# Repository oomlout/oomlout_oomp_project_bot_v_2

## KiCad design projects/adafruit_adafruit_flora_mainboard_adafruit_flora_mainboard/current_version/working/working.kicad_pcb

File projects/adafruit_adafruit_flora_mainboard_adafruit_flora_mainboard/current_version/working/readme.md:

# adafruit_flora_mainboard
 
## summary 
* id: adafruit_adafruit_flora_mainboard_adafruit_flora_mainboard
* user: adafruit
* name: adafruit_flora_mainboard
* board: adafruit_flora_mainboard
* repo: https://github.com/adafruit/Adafruit-Flora-Mainboard

* src_file_repo_sch: 
* src_file_repo_sch_link: https://github.com/adafruit/Adafruit-Flora-Mainboard/tree/master/
* full details link: https://github.com/oomlout/oomlout_oomp_project_bot_v_2/tree/main/projects/adafruit_adafruit_flora_mainboard_adafruit_flora_mainboard/current_version/working  

## schematic  
  
[schematic (pdf)](working_schematic.pdf) 

## pcb  

[board (pdf)](working.pdf)  

## working_bom
| Id | Designator | Footprint | Quantity | Designation | Supplier and ref |  | None | 
| --- | --- | --- | --- | --- | --- | --- | --- | 
| 1 | TXLED0,RXLED0 | CHIPLED_0805_NOOUTLINE | 2 | YELLOW |  |  | [''] | 
| 2 | R1,R2 | 0805-NO | 2 | 22 |  |  | [''] | 
| 3 | ON/OFF0 | EG1390 | 1 | EG1390 |  |  | [''] | 
| 4 | R4,R3 | _0805MP | 2 | 1K |  |  | [''] | 
| 5 | IC2 | SOT23-5L | 1 | MIC5225-3.3V |  |  | [''] | 
| 6 | TX0,RX0,UNK3.3VTAP0,UNK3V3TAP2,VCC2,GNDTAP0,GNDTAP2,SDA0,GND3TAP0,D6,IO9,SCL0,IO12,IO10 | SEWINGTAP_2.0 | 14 | SEWTAP-2.0IN |  |  | [''] | 
| 7 | C6,C4,C8,C7,C5 | 0805-NO | 5 | 10uF |  |  | [''] | 
| 8 | U$2,U$3,U$6 | FIDUCIAL_1MM | 3 | FIDUCIAL" |  |  | [''] | 
| 9 | U$1 | ADAFRUIT_5MM | 1 |  |  |  | [''] | 
| 10 | Y1 | RESONATOR-SMD | 1 | 8MHz |  |  | [''] | 
| 11 | R7 | _0805MP | 1 | 10K |  |  | [''] | 
| 12 | JP1 | 2X03 | 1 | ICSP |  |  | [''] | 
| 13 | R8 | 0805-NO | 1 | 150K |  |  | [''] | 
| 14 | D2,D1 | SOD-123 | 2 | SCHOTTKY |  |  | [''] | 
| 15 | CN1 | 4UCONN_20329 | 1 | MiniB USB |  |  | [''] | 
| 16 | LED1 | WS2812 | 1 | WS2812 |  |  | [''] | 
| 17 | BOOT0 | KMR2 | 1 | SPST_TACT-KMR2 |  |  | [''] | 
| 18 | C9 | _0805MP | 1 | 10uF |  |  | [''] | 
| 19 | R9 | 0805-NO | 1 | 10K |  |  | [''] | 
| 20 | R5,R6 | 0805-NO | 2 | 1K |  |  | [''] | 
| 21 | L0 | CHIPLED_0805_NOOUTLINE | 1 | RED |  |  | [''] | 
| 22 | BATT0 | JST-PH-2-SMT-RA | 1 | 3-9VDC |  |  | [''] | 
| 23 | PWR0 | CHIPLED_0805_NOOUTLINE | 1 | GREEN |  |  | [''] | 
| 24 | R10 | 0805-NO | 1 | 2.2K |  |  | [''] | 
| 25 | L1 | R1206 | 1 | 500mA |  |  | [''] | 
| 26 | T1 | SOT-23 | 1 | DMG3415 |  |  | [''] | 
| 27 | IC1 | TQFP44 | 1 | ATMEGA32U4-AU |  |  | [''] | 
| 28 | U$8 | SYMBOL_CE_5MM | 1 |  |  |  | [''] | 
| 29 | U$5 | PCBFEAT-REV-040 | 1 |  |  |  | [''] | 
| 30 | U$7 | SYMBOL_FCC_5MM | 1 |  |  |  | [''] | 
| 31 | U$4 | FLORAMED | 1 |  |  |  | [''] | 

## bom_schematic
| Ref | Qnty | Value | Cmp name | Footprint | Description | Vendor | DNP | 
| --- | --- | --- | --- | --- | --- | --- | --- | 
| BATT0 | 1 | 3-9VDC | JST_2PIN-SMT-RA | working:JST-PH-2-SMT-RA |  |  |  | 
| BOOT0 | 1 | SPST_TACT-KMR2 | SPST_TACT-KMR2 | working:KMR2 |  |  |  | 
| C4, C5, C6, C7, C8 | 5 | 10uF | CAP_CERAMIC0805-NOOUTLINE | working:0805-NO |  |  |  | 
| C9 | 1 | 10uF | RESISTOR_0805MP | working:_0805MP |  |  |  | 
| CN1 | 1 | MiniB USB | USBMICRO_20329 | working:4UCONN_20329 |  |  |  | 
| D1, D2 | 2 | SCHOTTKY | DIODESOD-123 | working:SOD-123 |  |  |  | 
| D6 | 1 | SEWTAP-2.0IN | SEWTAP-2.0IN | working:SEWINGTAP_2.0 |  |  |  | 
| GND3TAP0 | 1 | SEWTAP-2.0IN | SEWTAP-2.0IN | working:SEWINGTAP_2.0 |  |  |  | 
| GNDTAP0, GNDTAP2 | 2 | SEWTAP-2.0IN | SEWTAP-2.0IN | working:SEWINGTAP_2.0 |  |  |  | 
| IC1 | 1 | ATMEGA32U4-AU | ATMEGA32U4-AU | working:TQFP44 |  |  |  | 
| IC2 | 1 | LP298XS | LP298XS | working:SOT23-5L |  |  |  | 
| IO9, IO10, IO12 | 3 | SEWTAP-2.0IN | SEWTAP-2.0IN | working:SEWINGTAP_2.0 |  |  |  | 
| JP1 | 1 | ICSP | PINHD-2X3 | working:2X03 |  |  |  | 
| L0 | 1 | RED | LED0805_NOOUTLINE | working:CHIPLED_0805_NOOUTLINE |  |  |  | 
| L1 | 1 | 500mA | PTCFUSE-1206 | working:R1206 |  |  |  | 
| LED1 | 1 | WS2812 | WS2812 | working:WS2812 |  |  |  | 
| ON/OFF0 | 1 | EG1390 | DPDT-EG1390 | working:EG1390 |  |  |  | 
| PWR0 | 1 | GREEN | LED0805_NOOUTLINE | working:CHIPLED_0805_NOOUTLINE |  |  |  | 
| R1, R2 | 2 | 22 | RESISTOR0805_NOOUTLINE | working:0805-NO |  |  |  | 
| R3, R4 | 2 | 1K | RESISTOR_0805MP | working:_0805MP |  |  |  | 
| R5, R6 | 2 | 1K | RESISTOR0805_NOOUTLINE | working:0805-NO |  |  |  | 
| R7 | 1 | 10K | RESISTOR_0805MP | working:_0805MP |  |  |  | 
| R8 | 1 | 150K | RESISTOR0805_NOOUTLINE | working:0805-NO |  |  |  | 
| R9 | 1 | 10K | RESISTOR0805_NOOUTLINE | working:0805-NO |  |  |  | 
| R10 | 1 | 2.2K | RESISTOR0805_NOOUTLINE | working:0805-NO |  |  |  | 
| RX0 | 1 | SEWTAP-2.0IN | SEWTAP-2.0IN | working:SEWINGTAP_2.0 |  |  |  | 
| RXLED0 | 1 | YELLOW | LED0805_NOOUTLINE | working:CHIPLED_0805_NOOUTLINE |  |  |  | 
| SCL0 | 1 | SEWTAP-2.0IN | SEWTAP-2.0IN | working:SEWINGTAP_2.0 |  |  |  | 
| SDA0 | 1 | SEWTAP-2.0IN | SEWTAP-2.0IN | working:SEWINGTAP_2.0 |  |  |  | 
| T1 | 1 | DMG3415 | PMOSSOT23 | working:SOT-23 |  |  |  | 
| TX0 | 1 | SEWTAP-2.0IN | SEWTAP-2.0IN | working:SEWINGTAP_2.0 |  |  |  | 
| TXLED0 | 1 | YELLOW | LED0805_NOOUTLINE | working:CHIPLED_0805_NOOUTLINE |  |  |  | 
| U$2, U$3, U$6 | 3 | FIDUCIAL"" | FIDUCIAL{dblquote}{dblquote} | working:FIDUCIAL_1MM |  |  |  | 
| UNK3.3VTAP0 | 1 | SEWTAP-2.0IN | SEWTAP-2.0IN | working:SEWINGTAP_2.0 |  |  |  | 
| UNK3V3TAP2 | 1 | SEWTAP-2.0IN | SEWTAP-2.0IN | working:SEWINGTAP_2.0 |  |  |  | 
| VCC2 | 1 | SEWTAP-2.0IN | SEWTAP-2.0IN | working:SEWINGTAP_2.0 |  |  |  | 
| Y1 | 1 | RESONATORSMD | RESONATORSMD | working:RESONATOR-SMD |  |  |  |

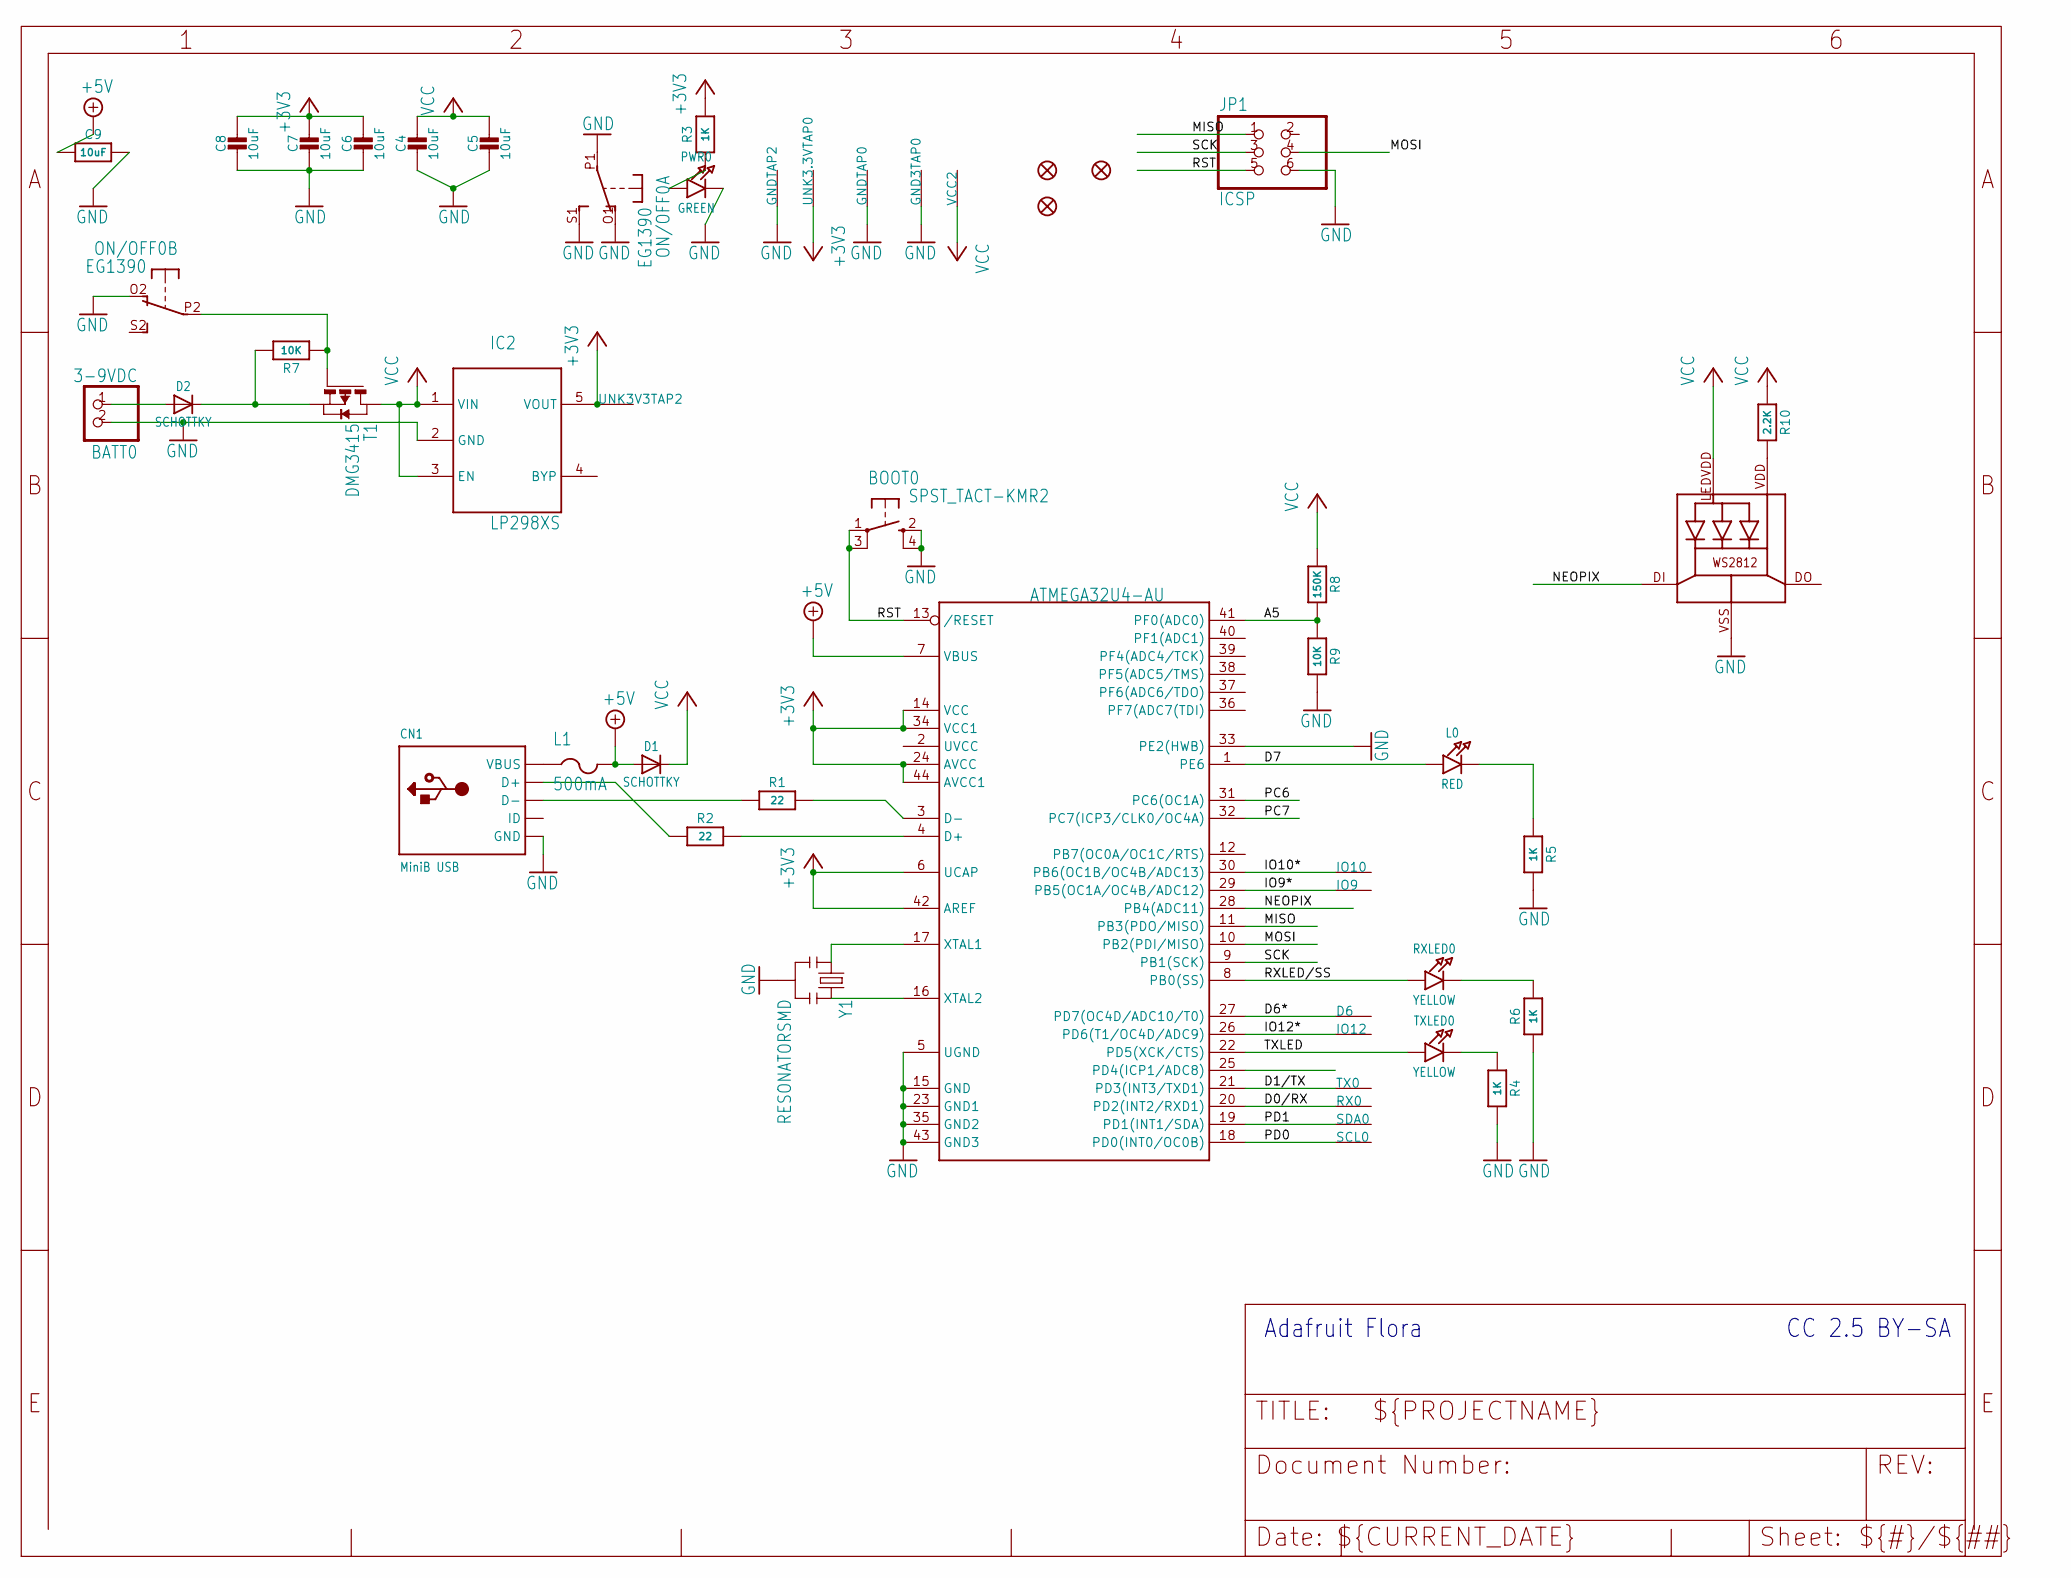
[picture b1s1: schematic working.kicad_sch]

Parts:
BATT0: 3-9VDC; JST-PH-2-SMT-RA
BOOT0: SPST_TACT-KMR2; KMR2
C4, C5, C6, C7, C8: 10uF; 0805-NO
C9: 10uF; _0805MP
CN1: MiniB USB; 4UCONN_20329
D1, D2: SCHOTTKY; SOD-123
D6: SEWTAP-2.0IN; SEWINGTAP_2.0
GND3TAP0: SEWTAP-2.0IN; SEWINGTAP_2.0
GNDTAP0, GNDTAP2: SEWTAP-2.0IN; SEWINGTAP_2.0
IC1: ATMEGA32U4-AU; TQFP44
IC2: LP298XS; SOT23-5L
IO9, IO10, IO12: SEWTAP-2.0IN; SEWINGTAP_2.0
JP1: ICSP; 2X03
L0: RED; CHIPLED_0805_NOOUTLINE
L1: 500mA; R1206
LED1: WS2812
ON/OFF0: EG1390
PWR0: GREEN; CHIPLED_0805_NOOUTLINE
R1, R2: 22; 0805-NO
R3, R4: 1K; _0805MP
R5, R6: 1K; 0805-NO
R7: 10K; _0805MP
R8: 150K; 0805-NO
R9: 10K; 0805-NO
R10: 2.2K; 0805-NO
RX0: SEWTAP-2.0IN; SEWINGTAP_2.0
RXLED0: YELLOW; CHIPLED_0805_NOOUTLINE
SCL0: SEWTAP-2.0IN; SEWINGTAP_2.0
SDA0: SEWTAP-2.0IN; SEWINGTAP_2.0
T1: DMG3415; SOT-23
TX0: SEWTAP-2.0IN; SEWINGTAP_2.0
TXLED0: YELLOW; CHIPLED_0805_NOOUTLINE
U$2, U$3, U$6: FIDUCIAL""; FIDUCIAL_1MM
UNK3.3VTAP0, UNK3V3TAP2: SEWTAP-2.0IN; SEWINGTAP_2.0
VCC2: SEWTAP-2.0IN; SEWINGTAP_2.0
Y1: RESONATORSMD; RESONATOR-SMD

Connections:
+3V3: C6.1, C7.1, C8.1, IC1.6 (UCAP), IC1.14 (VCC), IC1.24 (AVCC), IC1.34 (VCC1), IC1.42 (AREF), IC1.44 (AVCC1), IC2.5 (VOUT), R3.2, UNK3.3VTAP0.P$1, UNK3V3TAP2.P$1
+5V: C9.1, D1.A, IC1.7 (VBUS), L1.2
A5: IC1.41 (PF0(ADC0)), R8.2, R9.1
D0/RX: IC1.20 (PD2(INT2/RXD1)), RX0.P$1
D1/TX: IC1.21 (PD3(INT3/TXD1)), TX0.P$1
D6*: D6.P$1, IC1.27 (PD7(OC4D/ADC10/T0))
D7: IC1.1 (PE6), L0.A
GND: BATT0.2 (1), BOOT0.2 (S), BOOT0.4 (S1), C4.2, C5.2, C6.2, C7.2, C8.2, C9.2, CN1.BASE@1 (GND), CN1.BASE@2 (GND), CN1.GND, CN1.SPRT@1 (GND), CN1.SPRT@2 (GND), CN1.SPRT@3 (GND), CN1.SPRT@4 (GND), GND3TAP0.P$1, GNDTAP0.P$1, GNDTAP2.P$1, IC1.5 (UGND), IC1.15 (GND), IC1.23 (GND1), IC1.33 (PE2(HWB)), IC1.35 (GND2), IC1.43 (GND3), IC2.2 (GND), JP1.6, LED1.VSS (GND), ON/OFF0.O1 (O), ON/OFF0.O2 (O), ON/OFF0.P1, ON/OFF0.S1 (S), PWR0.C, R4.2, R5.2, R6.1, R9.2, Y1.2
IO9*: IC1.29 (PB5(OC1A/OC4B/ADC12)), IO9.P$1
IO10*: IC1.30 (PB6(OC1B/OC4B/ADC13)), IO10.P$1
IO12*: IC1.26 (PD6(T1/OC4D/ADC9)), IO12.P$1
MISO: IC1.11 (PB3(PDO/MISO)), JP1.1
MOSI: IC1.10 (PB2(PDI/MISO)), JP1.4
unnamed: PWR0.A, R3.1
unnamed: CN1.D+, R2.1
unnamed: IC1.3 (D-), R1.2
unnamed: IC1.4 (D+), R2.2
unnamed: CN1.D-, R1.1
unnamed: D2.C, R7.2, T1.2 (S)
unnamed: BATT0.1 (2), D2.A
unnamed: IC1.17 (XTAL1), Y1.1
unnamed: IC1.16 (XTAL2), Y1.3
unnamed: L0.C, R5.1
unnamed: R4.1, TXLED0.C
unnamed: R6.2, RXLED0.C
unnamed: ON/OFF0.P2, R7.1, T1.3 (G)
unnamed: LED1.VDD, R10.2
NEOPIX: IC1.28 (PB4(ADC11)), LED1.DI
PC6: IC1.31 (PC6(OC1A))
PC7: IC1.32 (PC7(ICP3/CLK0/OC4A))
PD0: IC1.18 (PD0(INT0/OC0B)), SCL0.P$1
PD1: IC1.19 (PD1(INT1/SDA)), SDA0.P$1
RST: BOOT0.1, BOOT0.3 (P1), IC1.13 (/RESET), JP1.5
RXLED/SS: IC1.8 (PB0(SS)), RXLED0.A
SCK: IC1.9 (PB1(SCK)), JP1.3
TXLED: IC1.22 (PD5(XCK/CTS)), TXLED0.A
VBUS: CN1.VBUS, L1.1
VCC: C4.1, C5.1, D1.C, IC2.1 (VIN), IC2.3 (EN), LED1.LEDVDD, R8.1, R10.1, T1.1 (D), VCC2.P$1

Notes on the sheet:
CC 2.5 BY-SA
Adafruit Flora

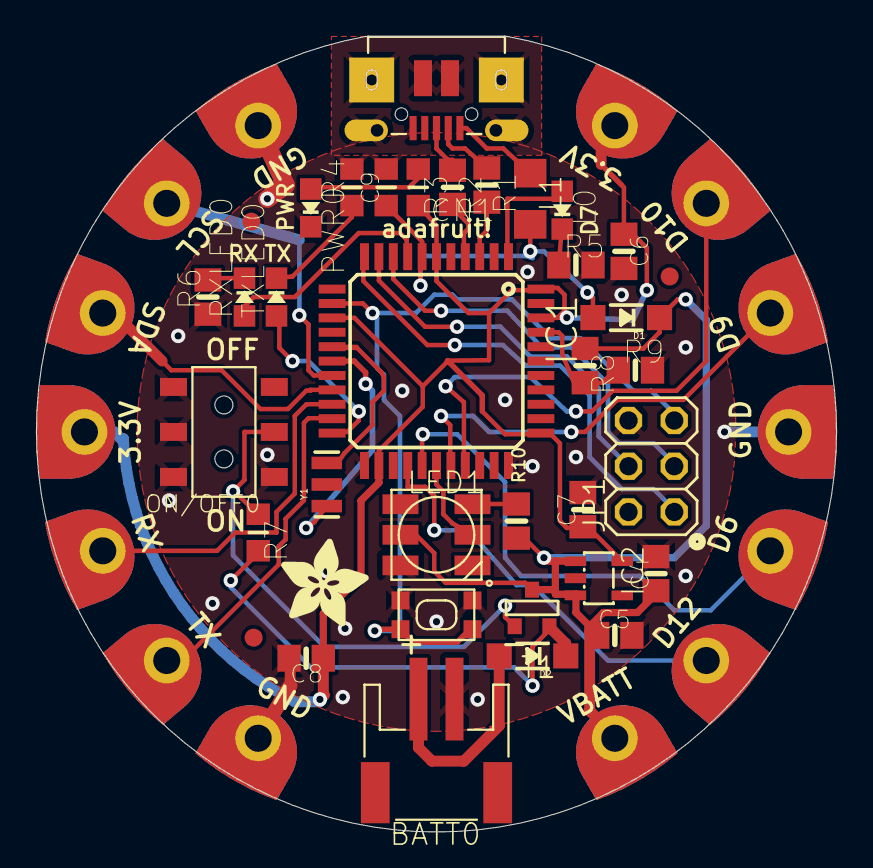
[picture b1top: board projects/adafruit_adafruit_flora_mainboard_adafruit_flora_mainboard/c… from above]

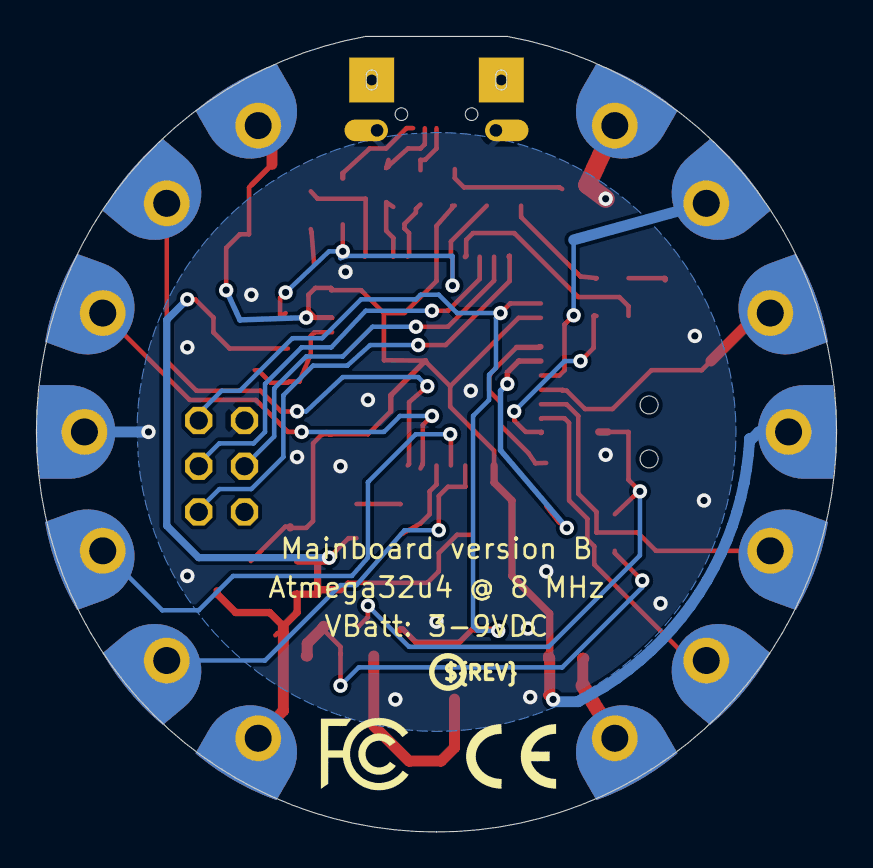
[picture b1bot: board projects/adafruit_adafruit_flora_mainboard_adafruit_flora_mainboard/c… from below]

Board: 16 copper layers, 44.5 x 44.2 mm, 55 parts (4 on the bottom side), 36 nets.

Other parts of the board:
U$1: ADAFRUIT_5MM
U$4: FLORAMED
U$5: PCBFEAT-REV-040
U$7: SYMBOL_FCC_5MM
U$8: SYMBOL_CE_5MM

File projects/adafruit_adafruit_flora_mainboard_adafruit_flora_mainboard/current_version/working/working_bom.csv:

"Id";"Designator";"Footprint";"Quantity";"Designation";"Supplier and ref";
1;"TXLED0,RXLED0";"CHIPLED_0805_NOOUTLINE";2;"YELLOW";;;
2;"R1,R2";"0805-NO";2;"22";;;
3;"ON/OFF0";"EG1390";1;"EG1390";;;
4;"R4,R3";"_0805MP";2;"1K";;;
5;"IC2";"SOT23-5L";1;"MIC5225-3.3V";;;
6;"TX0,RX0,UNK3.3VTAP0,UNK3V3TAP2,VCC2,GNDTAP0,GNDTAP2,SDA0,GND3TAP0,D6,IO9,SCL0,IO12,IO10";"SEWINGTAP_2.0";14;"SEWTAP-2.0IN";;;
7;"C6,C4,C8,C7,C5";"0805-NO";5;"10uF";;;
8;"U$2,U$3,U$6";"FIDUCIAL_1MM";3;"FIDUCIAL""";;;
9;"U$1";"ADAFRUIT_5MM";1;"";;;
10;"Y1";"RESONATOR-SMD";1;"8MHz";;;
11;"R7";"_0805MP";1;"10K";;;
12;"JP1";"2X03";1;"ICSP";;;
13;"R8";"0805-NO";1;"150K";;;
14;"D2,D1";"SOD-123";2;"SCHOTTKY";;;
15;"CN1";"4UCONN_20329";1;"MiniB USB";;;
16;"LED1";"WS2812";1;"WS2812";;;
17;"BOOT0";"KMR2";1;"SPST_TACT-KMR2";;;
18;"C9";"_0805MP";1;"10uF";;;
19;"R9";"0805-NO";1;"10K";;;
20;"R5,R6";"0805-NO";2;"1K";;;
21;"L0";"CHIPLED_0805_NOOUTLINE";1;"RED";;;
22;"BATT0";"JST-PH-2-SMT-RA";1;"3-9VDC";;;
23;"PWR0";"CHIPLED_0805_NOOUTLINE";1;"GREEN";;;
24;"R10";"0805-NO";1;"2.2K";;;
25;"L1";"R1206";1;"500mA";;;
26;"T1";"SOT-23";1;"DMG3415";;;
27;"IC1";"TQFP44";1;"ATMEGA32U4-AU";;;
28;"U$8";"SYMBOL_CE_5MM";1;"";;;
29;"U$5";"PCBFEAT-REV-040";1;"";;;
30;"U$7";"SYMBOL_FCC_5MM";1;"";;;
31;"U$4";"FLORAMED";1;"";;;

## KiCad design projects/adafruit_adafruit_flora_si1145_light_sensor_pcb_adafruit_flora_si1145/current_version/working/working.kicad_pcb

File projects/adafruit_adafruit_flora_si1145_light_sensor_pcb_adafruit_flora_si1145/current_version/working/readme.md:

# adafruit_flora_si1145_light_sensor_pcb
 
## summary 
* id: adafruit_adafruit_flora_si1145_light_sensor_pcb_adafruit_flora_si1145
* user: adafruit
* name: adafruit_flora_si1145_light_sensor_pcb
* board: adafruit_flora_si1145
* repo: https://github.com/adafruit/Adafruit-Flora-Si1145-Light-Sensor-PCB

* src_file_repo_sch: 
* src_file_repo_sch_link: https://github.com/adafruit/Adafruit-Flora-Si1145-Light-Sensor-PCB/tree/master/
* full details link: https://github.com/oomlout/oomlout_oomp_project_bot_v_2/tree/main/projects/adafruit_adafruit_flora_si1145_light_sensor_pcb_adafruit_flora_si1145/current_version/working  

## schematic  
  
[schematic (pdf)](working_schematic.pdf) 

## pcb  

[board (pdf)](working.pdf)  

## working_bom
| Id | Designator | Footprint | Quantity | Designation | Supplier and ref |  | None | 
| --- | --- | --- | --- | --- | --- | --- | --- | 
| 1 | R3,R2 | 0805-NO | 2 | 10K |  |  | [''] | 
| 2 | U$4,U$3 | ADAFRUIT_2.5MM | 2 |  |  |  | [''] | 
| 3 | SCL2,VCC0,SDA1,SCL1,SDA2,GND0 | SEWINGTAP_0.5 | 6 | SEWTAP0.5IN |  |  | [''] | 
| 4 | FID2,FID1 | FIDUCIAL_1MM | 2 | FIDUCIAL" |  |  | [''] | 
| 5 | C2 | 0805-NO | 1 | 10uF |  |  | [''] | 
| 6 | U1 | SI114X | 1 | SI1145 |  |  | [''] | 

## bom_schematic
| Ref | Qnty | Value | Cmp name | Footprint | Description | Vendor | DNP | 
| --- | --- | --- | --- | --- | --- | --- | --- | 
| C2 | 1 | 10uF | CAP_CERAMIC0805-NOOUTLINE | working:0805-NO |  |  |  | 
| FID1, FID2 | 2 | FIDUCIAL"" | FIDUCIAL{dblquote}{dblquote} | working:FIDUCIAL_1MM |  |  |  | 
| GND0 | 1 | SEWTAP0.5IN | SEWTAP0.5IN | working:SEWINGTAP_0.5 |  |  |  | 
| R2, R3 | 2 | 10K | RESISTOR0805_NOOUTLINE | working:0805-NO |  |  |  | 
| SCL1, SCL2 | 2 | SEWTAP0.5IN | SEWTAP0.5IN | working:SEWINGTAP_0.5 |  |  |  | 
| SDA1, SDA2 | 2 | SEWTAP0.5IN | SEWTAP0.5IN | working:SEWINGTAP_0.5 |  |  |  | 
| U1 | 1 | SI1145 | SI114X | working:SI114X |  |  |  | 
| VCC0 | 1 | SEWTAP0.5IN | SEWTAP0.5IN | working:SEWINGTAP_0.5 |  |  |  |

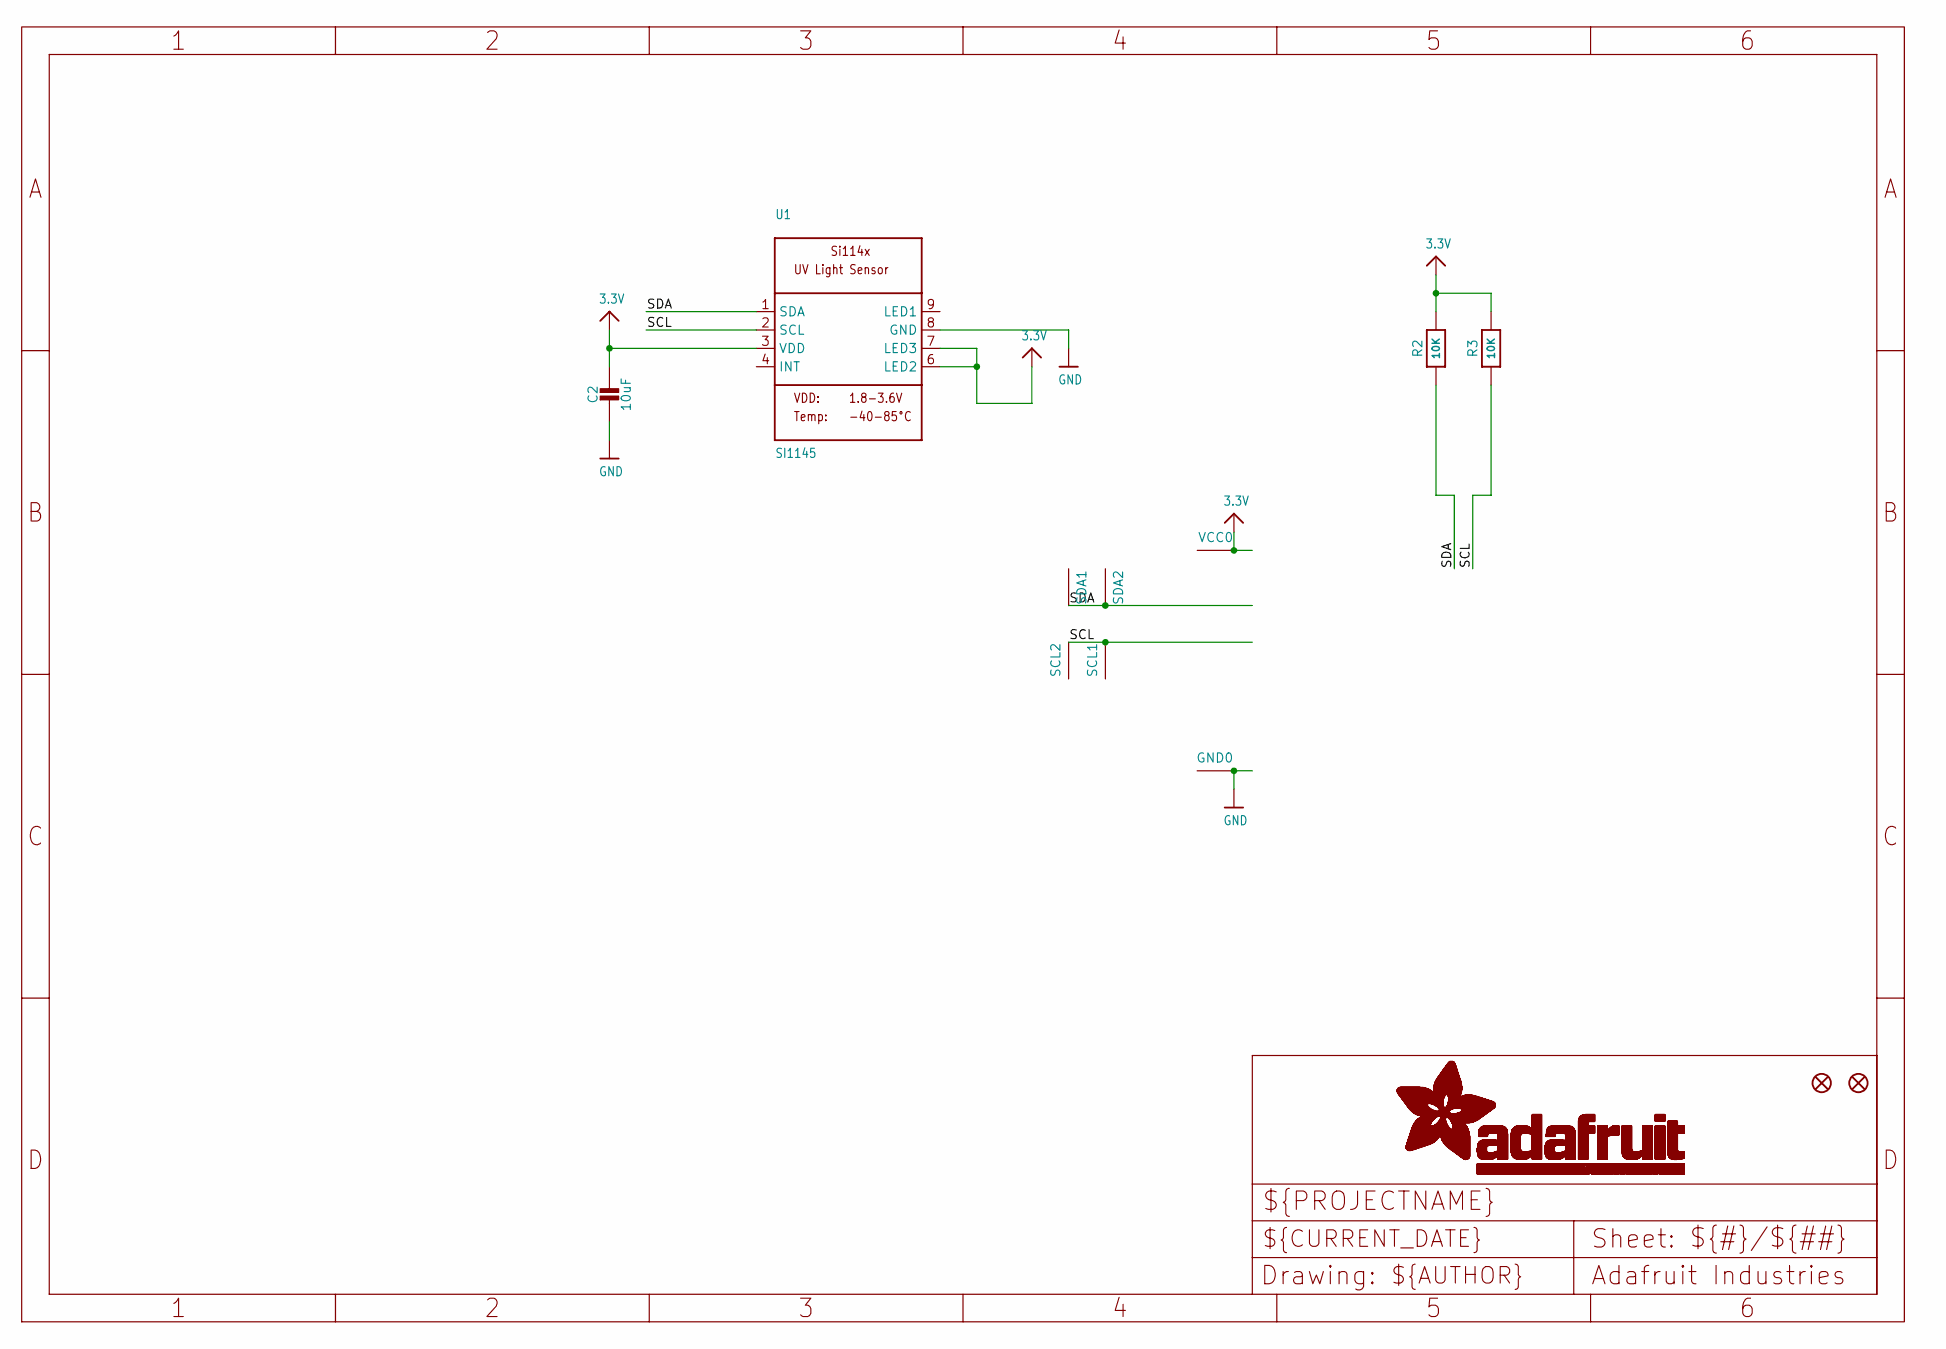
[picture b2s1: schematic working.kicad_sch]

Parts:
C2: 10uF; 0805-NO
FID1, FID2: FIDUCIAL""; FIDUCIAL_1MM
GND0: SEWTAP0.5IN; SEWINGTAP_0.5
R2, R3: 10K; 0805-NO
SCL1, SCL2: SEWTAP0.5IN; SEWINGTAP_0.5
SDA1, SDA2: SEWTAP0.5IN; SEWINGTAP_0.5
U1: SI1145; SI114X
VCC0: SEWTAP0.5IN; SEWINGTAP_0.5

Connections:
3.3V: C2.1, R2.2, R3.2, U1.3 (VDD), U1.6 (LED2), U1.7 (LED3), VCC0.TAP
GND: C2.2, GND0.TAP, U1.8 (GND)
SCL: R3.1, SCL1.TAP, SCL2.TAP, U1.2 (SCL)
SDA: R2.1, SDA1.TAP, SDA2.TAP, U1.1 (SDA)

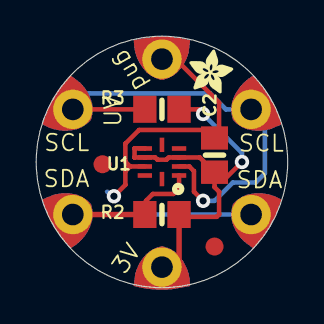
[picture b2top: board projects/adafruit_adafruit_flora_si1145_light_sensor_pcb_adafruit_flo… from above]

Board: 2 copper layers, 14.0 x 14.0 mm, 14 parts (1 on the bottom side), 4 nets.

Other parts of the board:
U$3, U$4: ADAFRUIT_2.5MM

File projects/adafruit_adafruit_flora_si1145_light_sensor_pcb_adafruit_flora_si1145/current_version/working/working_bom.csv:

"Id";"Designator";"Footprint";"Quantity";"Designation";"Supplier and ref";
1;"R3,R2";"0805-NO";2;"10K";;;
2;"U$4,U$3";"ADAFRUIT_2.5MM";2;"";;;
3;"SCL2,VCC0,SDA1,SCL1,SDA2,GND0";"SEWINGTAP_0.5";6;"SEWTAP0.5IN";;;
4;"FID2,FID1";"FIDUCIAL_1MM";2;"FIDUCIAL""";;;
5;"C2";"0805-NO";1;"10uF";;;
6;"U1";"SI114X";1;"SI1145";;;

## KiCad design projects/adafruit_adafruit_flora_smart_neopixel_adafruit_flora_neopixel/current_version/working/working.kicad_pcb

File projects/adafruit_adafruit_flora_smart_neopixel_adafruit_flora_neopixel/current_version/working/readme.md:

# adafruit_flora_smart_neopixel
 
## summary 
* id: adafruit_adafruit_flora_smart_neopixel_adafruit_flora_neopixel
* user: adafruit
* name: adafruit_flora_smart_neopixel
* board: adafruit_flora_neopixel
* repo: https://github.com/adafruit/Adafruit-Flora-Smart-NeoPixel

* src_file_repo_sch: 
* src_file_repo_sch_link: https://github.com/adafruit/Adafruit-Flora-Smart-NeoPixel/tree/master/
* full details link: https://github.com/oomlout/oomlout_oomp_project_bot_v_2/tree/main/projects/adafruit_adafruit_flora_smart_neopixel_adafruit_flora_neopixel/current_version/working  

## pcb  

[board (pdf)](working.pdf)  

## working_bom
| Id | Designator | Footprint | Quantity | Designation | Supplier and ref |  | None | 
| --- | --- | --- | --- | --- | --- | --- | --- | 
| 1 | LED2 | RGBLED5050 | 1 | RGBLED5050 |  |  | [''] | 
| 2 | GND0,DATA_OUTPUT0,DATA_INPUT0,VDD0 | SEWINGTAP_0.5 | 4 | SEWTAP0.5IN |  |  | [''] | 
| 3 | R2,R3 | R0805 | 2 | 22 |  |  | [''] | 
| 4 | R1 | R0805 | 1 | 1.0K |  |  | [''] | 
| 5 | C1 | C0805K | 1 | 1uF |  |  | [''] | 
| 6 | IC2 | SO08-SKINNYPADS | 1 | WS2811-SOP8 |  |  | [''] |

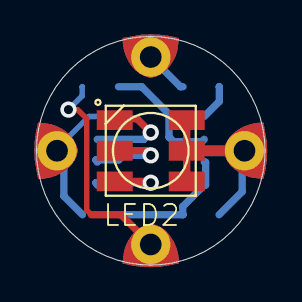
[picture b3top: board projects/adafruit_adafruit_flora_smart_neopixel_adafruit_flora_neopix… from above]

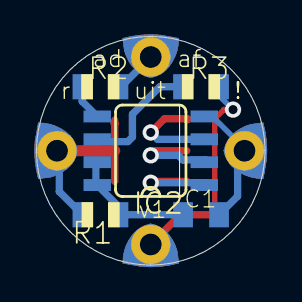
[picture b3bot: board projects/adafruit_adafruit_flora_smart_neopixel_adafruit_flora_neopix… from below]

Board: 16 copper layers, 12.7 x 12.7 mm, 10 parts (5 on the bottom side), 10 nets.

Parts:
C1: 1uF; C0805K
DATA_INPUT0: SEWTAP0.5IN; SEWINGTAP_0.5
DATA_OUTPUT0: SEWTAP0.5IN; SEWINGTAP_0.5
GND0: SEWTAP0.5IN; SEWINGTAP_0.5
IC2: WS2811-SOP8; SO08-SKINNYPADS
LED2: RGBLED5050
R1: 1.0K; R0805
R2, R3: 22; R0805
VDD0: SEWTAP0.5IN; SEWINGTAP_0.5

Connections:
GND: C1.2, GND0.TAP, IC2.4
unnamed: IC2.3, LED2.4
unnamed: IC2.2, LED2.5
unnamed: IC2.1, LED2.6
unnamed: IC2.6, R3.1
unnamed: IC2.5, R2.1
unnamed: DATA_INPUT0.TAP, R3.2
unnamed: DATA_OUTPUT0.TAP, R2.2
unnamed: C1.1, IC2.7, IC2.8, R1.1
VDD: LED2.1, LED2.2, LED2.3, R1.2, VDD0.TAP

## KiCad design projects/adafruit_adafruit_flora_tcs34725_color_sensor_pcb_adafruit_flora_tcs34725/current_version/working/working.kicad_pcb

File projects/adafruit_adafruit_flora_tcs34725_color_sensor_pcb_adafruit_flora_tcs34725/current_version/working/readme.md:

# adafruit_flora_tcs34725_color_sensor_pcb
 
## summary 
* id: adafruit_adafruit_flora_tcs34725_color_sensor_pcb_adafruit_flora_tcs34725
* user: adafruit
* name: adafruit_flora_tcs34725_color_sensor_pcb
* board: adafruit_flora_tcs34725
* repo: https://github.com/adafruit/Adafruit-Flora-TCS34725-Color-Sensor-PCB

* src_file_repo_sch: 
* src_file_repo_sch_link: https://github.com/adafruit/Adafruit-Flora-TCS34725-Color-Sensor-PCB/tree/master/
* full details link: https://github.com/oomlout/oomlout_oomp_project_bot_v_2/tree/main/projects/adafruit_adafruit_flora_tcs34725_color_sensor_pcb_adafruit_flora_tcs34725/current_version/working  

## schematic  
  
[schematic (pdf)](working_schematic.pdf) 

## pcb  

[board (pdf)](working.pdf)  

## working_bom
| Id | Designator | Footprint | Quantity | Designation | Supplier and ref |  | None | 
| --- | --- | --- | --- | --- | --- | --- | --- | 
| 1 | Q3 | SOT23-WIDE | 1 | BSS138 |  |  | [''] | 
| 2 | TP3,TP1,TP2,TP4,TP5,TP6 | SEWINGTAP_0.5 | 6 | SEWTAP0.5IN |  |  | [''] | 
| 3 | U1 | TCS3472_FN6 | 1 | TCS34725 |  |  | [''] | 
| 4 | R1,R6,R2 | _0805 | 3 | 10K |  |  | [''] | 
| 5 | FID1,FID2 | FIDUCIAL_1MM | 2 | FIDUCIAL" |  |  | [''] | 
| 6 | LED1 | EVERLIGHT_45-21 | 1 | 45-21/LK2C-B38452C4CB2/2T |  |  | [''] | 
| 7 | C1 | _0805 | 1 | 0.1ÂµF |  |  | [''] | 
| 8 | U$8 | ADAFRUIT_3.5MM | 1 |  |  |  | [''] | 

## bom_schematic
| Ref | Qnty | Value | Cmp name | Footprint | Description | Vendor | DNP | 
| --- | --- | --- | --- | --- | --- | --- | --- | 
| C1 | 1 | 0.1ÂµF | CAP_CERAMIC_0805 | working:_0805 |  |  |  | 
| FID1, FID2 | 2 | FIDUCIAL"" | FIDUCIAL{dblquote}{dblquote} | working:FIDUCIAL_1MM |  |  |  | 
| LED1 | 1 | 45-21/LK2C-B38452C4CB2/2T | LEDEV45-21 | working:EVERLIGHT_45-21 |  |  |  | 
| Q3 | 1 | BSS138 | MOSFET-NWIDE | working:SOT23-WIDE |  |  |  | 
| R1, R2, R6 | 3 | 10K | RESISTOR_0805 | working:_0805 |  |  |  | 
| TP1, TP2, TP3, TP4, TP5, TP6 | 6 | SEWTAP0.5IN | SEWTAP0.5IN | working:SEWINGTAP_0.5 |  |  |  | 
| U1 | 1 | TCS34725 | LIGHT_TCS3472 | working:TCS3472_FN6 |  |  |  |

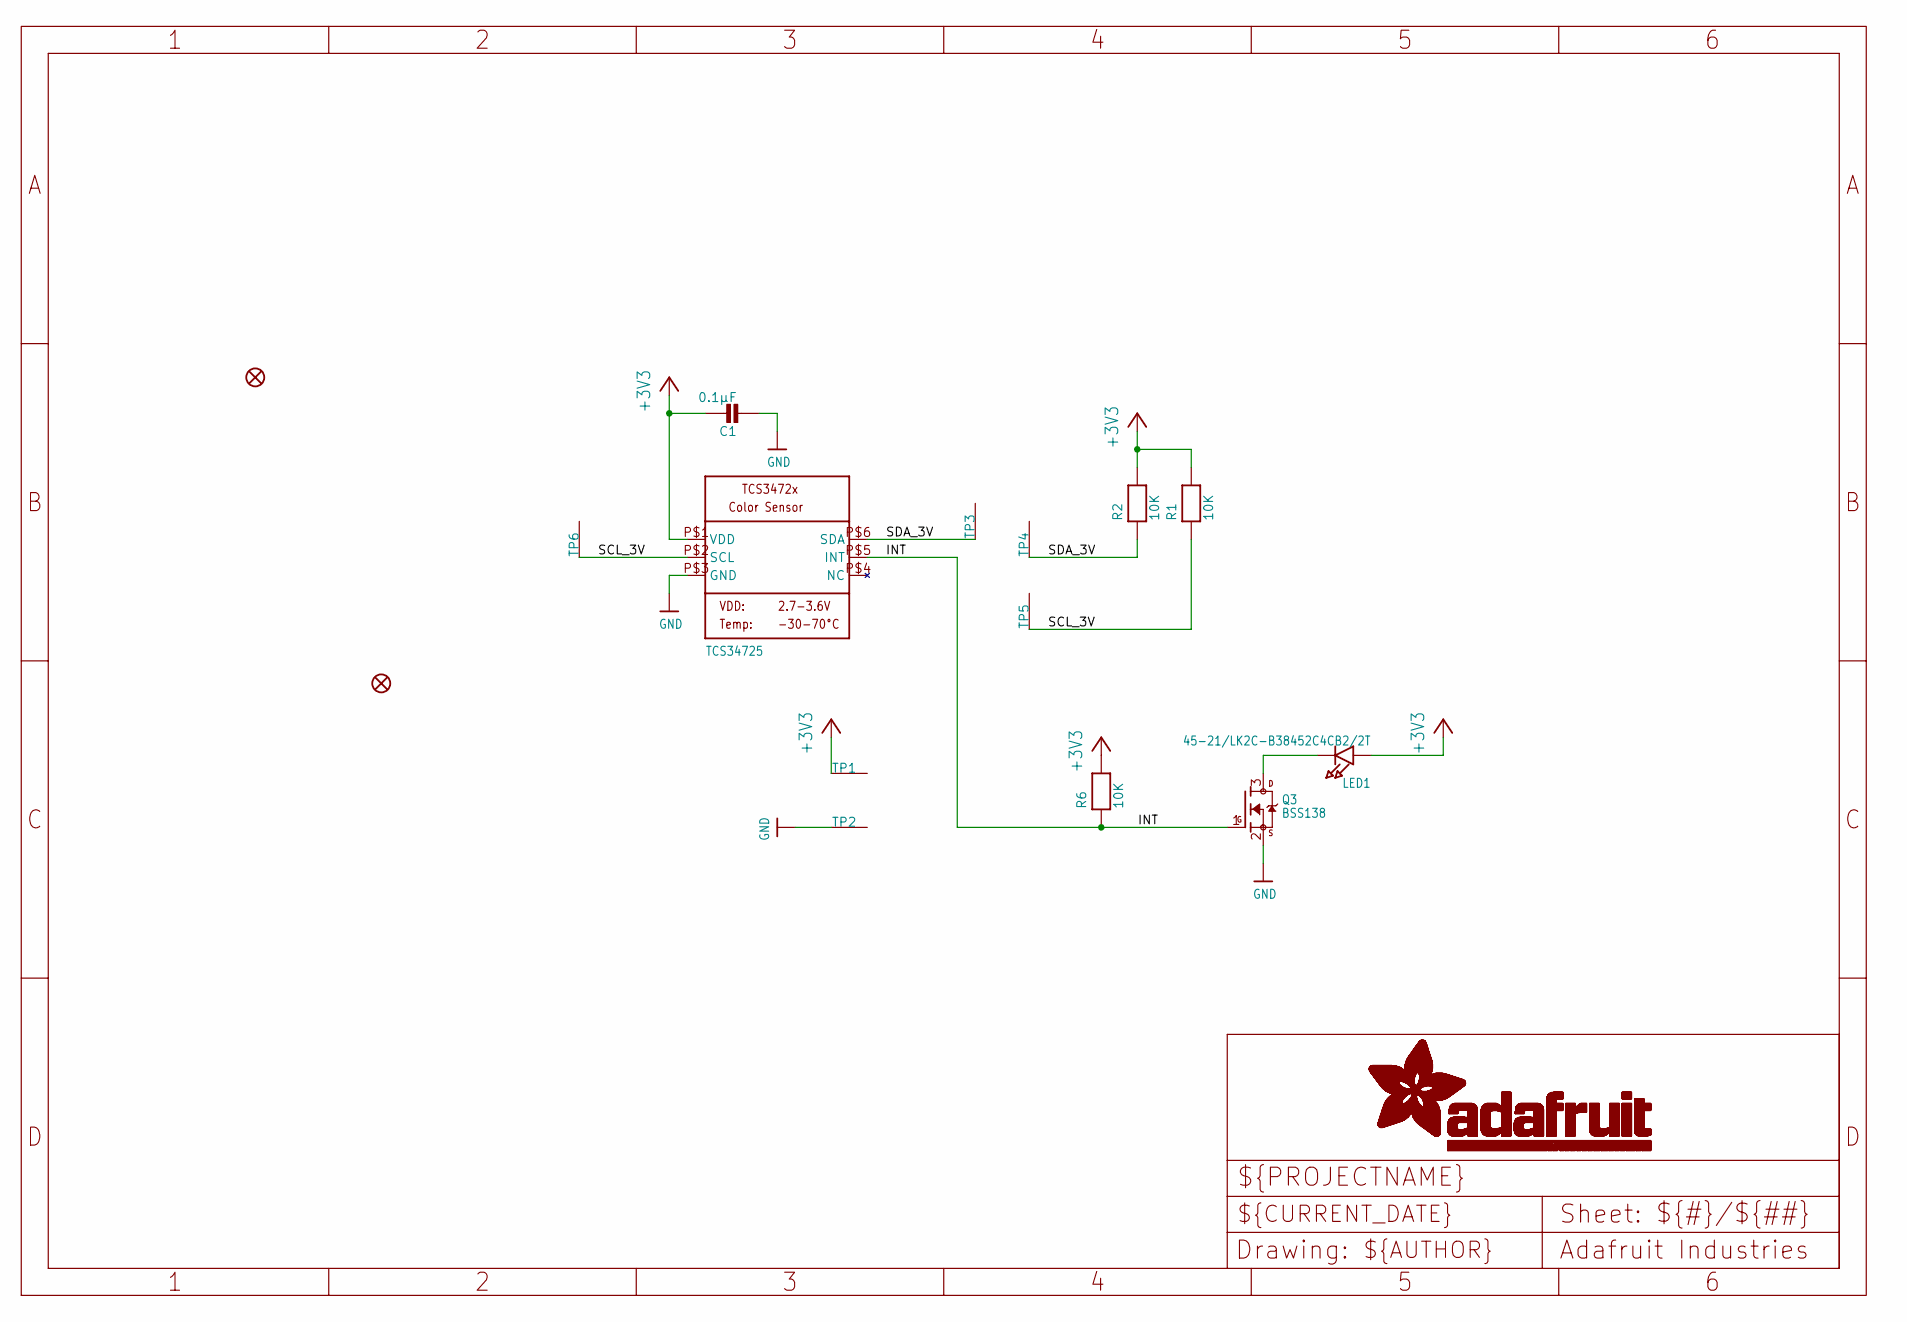
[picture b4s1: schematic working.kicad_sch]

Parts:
C1: 0.1µF; _0805
FID1, FID2: FIDUCIAL""; FIDUCIAL_1MM
LED1: 45-21/LK2C-B38452C4CB2/2T; EVERLIGHT_45-21
Q3: BSS138; SOT23-WIDE
R1, R2, R6: 10K; _0805
TP1, TP2, TP3, TP4, TP5, TP6: SEWTAP0.5IN; SEWINGTAP_0.5
U1: TCS34725; TCS3472_FN6

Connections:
+3V3: C1.1, LED1.A, R1.2, R2.2, R6.2, TP1.TAP, U1.P$1 (VDD)
GND: C1.2, Q3.2 (S), TP2.TAP, U1.P$3 (GND)
INT: Q3.1 (G), R6.1, U1.P$5 (INT)
unnamed: LED1.K (C), Q3.3 (D)
SCL_3V: R1.1, TP5.TAP, TP6.TAP, U1.P$2 (SCL)
SDA_3V: R2.1, TP3.TAP, TP4.TAP, U1.P$6 (SDA)

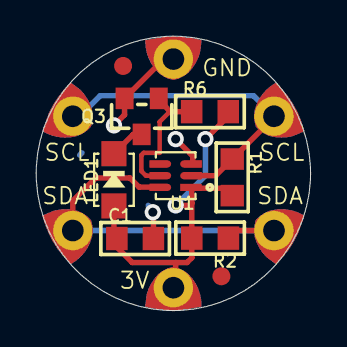
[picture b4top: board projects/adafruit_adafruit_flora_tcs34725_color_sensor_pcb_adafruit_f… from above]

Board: 2 copper layers, 15.2 x 15.2 mm, 16 parts (1 on the bottom side), 6 nets.

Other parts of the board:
U$8: ADAFRUIT_3.5MM

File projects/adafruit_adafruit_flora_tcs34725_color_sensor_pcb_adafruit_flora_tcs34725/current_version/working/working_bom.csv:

"Id";"Designator";"Footprint";"Quantity";"Designation";"Supplier and ref";
1;"Q3";"SOT23-WIDE";1;"BSS138";;;
2;"TP3,TP1,TP2,TP4,TP5,TP6";"SEWINGTAP_0.5";6;"SEWTAP0.5IN";;;
3;"U1";"TCS3472_FN6";1;"TCS34725";;;
4;"R1,R6,R2";"_0805";3;"10K";;;
5;"FID1,FID2";"FIDUCIAL_1MM";2;"FIDUCIAL""";;;
6;"LED1";"EVERLIGHT_45-21";1;"45-21/LK2C-B38452C4CB2/2T";;;
7;"C1";"_0805";1;"0.1µF";;;
8;"U$8";"ADAFRUIT_3.5MM";1;"";;;

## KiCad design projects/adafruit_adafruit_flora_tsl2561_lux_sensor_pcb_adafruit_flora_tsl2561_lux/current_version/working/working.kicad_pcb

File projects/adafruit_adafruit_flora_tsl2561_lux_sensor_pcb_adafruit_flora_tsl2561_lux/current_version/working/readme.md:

# adafruit_flora_tsl2561_lux_sensor_pcb
 
## summary 
* id: adafruit_adafruit_flora_tsl2561_lux_sensor_pcb_adafruit_flora_tsl2561_lux
* user: adafruit
* name: adafruit_flora_tsl2561_lux_sensor_pcb
* board: adafruit_flora_tsl2561_lux
* repo: https://github.com/adafruit/Adafruit-Flora-TSL2561-Lux-Sensor-PCB

* src_file_repo_sch: 
* src_file_repo_sch_link: https://github.com/adafruit/Adafruit-Flora-TSL2561-Lux-Sensor-PCB/tree/master/
* full details link: https://github.com/oomlout/oomlout_oomp_project_bot_v_2/tree/main/projects/adafruit_adafruit_flora_tsl2561_lux_sensor_pcb_adafruit_flora_tsl2561_lux/current_version/working  

## schematic  
  
[schematic (pdf)](working_schematic.pdf) 

## pcb  

[board (pdf)](working.pdf)  

## working_bom
| Id | Designator | Footprint | Quantity | Designation | Supplier and ref |  | None | 
| --- | --- | --- | --- | --- | --- | --- | --- | 
| 1 | SDA1,SCL1,SCL2,SDA2,VCC0,GND0 | SEWINGTAP_0.5 | 6 | SEWTAP0.5IN |  |  | [''] | 
| 2 | R3,R2 | _0805 | 2 | 10K |  |  | [''] | 
| 3 | U$4,U$3 | ADAFRUIT_2.5MM | 2 |  |  |  | [''] | 
| 4 | U2 | TSL2561_FN | 1 | TSL2561 |  |  | [''] | 
| 5 | FID2,FID1 | FIDUCIAL_1MM | 2 | FIDUCIAL" |  |  | [''] | 
| 6 | C1 | C0805K | 1 | 0.1uF |  |  | [''] | 
| 7 | SJ1 | SJ_2 | 1 |  |  |  | [''] | 

## bom_schematic
| Ref | Qnty | Value | Cmp name | Footprint | Description | Vendor | DNP | 
| --- | --- | --- | --- | --- | --- | --- | --- | 
| C1 | 1 | 0.1uF | C-USC0805K | working:C0805K |  |  |  | 
| FID1, FID2 | 2 | FIDUCIAL"" | FIDUCIAL{dblquote}{dblquote} | working:FIDUCIAL_1MM |  |  |  | 
| GND0 | 1 | SEWTAP0.5IN | SEWTAP0.5IN | working:SEWINGTAP_0.5 |  |  |  | 
| R2, R3 | 2 | 10K | RESISTOR_0805 | working:_0805 |  |  |  | 
| SCL1, SCL2 | 2 | SEWTAP0.5IN | SEWTAP0.5IN | working:SEWINGTAP_0.5 |  |  |  | 
| SDA1, SDA2 | 2 | SEWTAP0.5IN | SEWTAP0.5IN | working:SEWINGTAP_0.5 |  |  |  | 
| SJ1 | 1 | SJ2W | SJ2W | working:SJ_2 |  |  |  | 
| U2 | 1 | TSL2561 | TSL2561 | working:TSL2561_FN |  |  |  | 
| VCC0 | 1 | SEWTAP0.5IN | SEWTAP0.5IN | working:SEWINGTAP_0.5 |  |  |  |

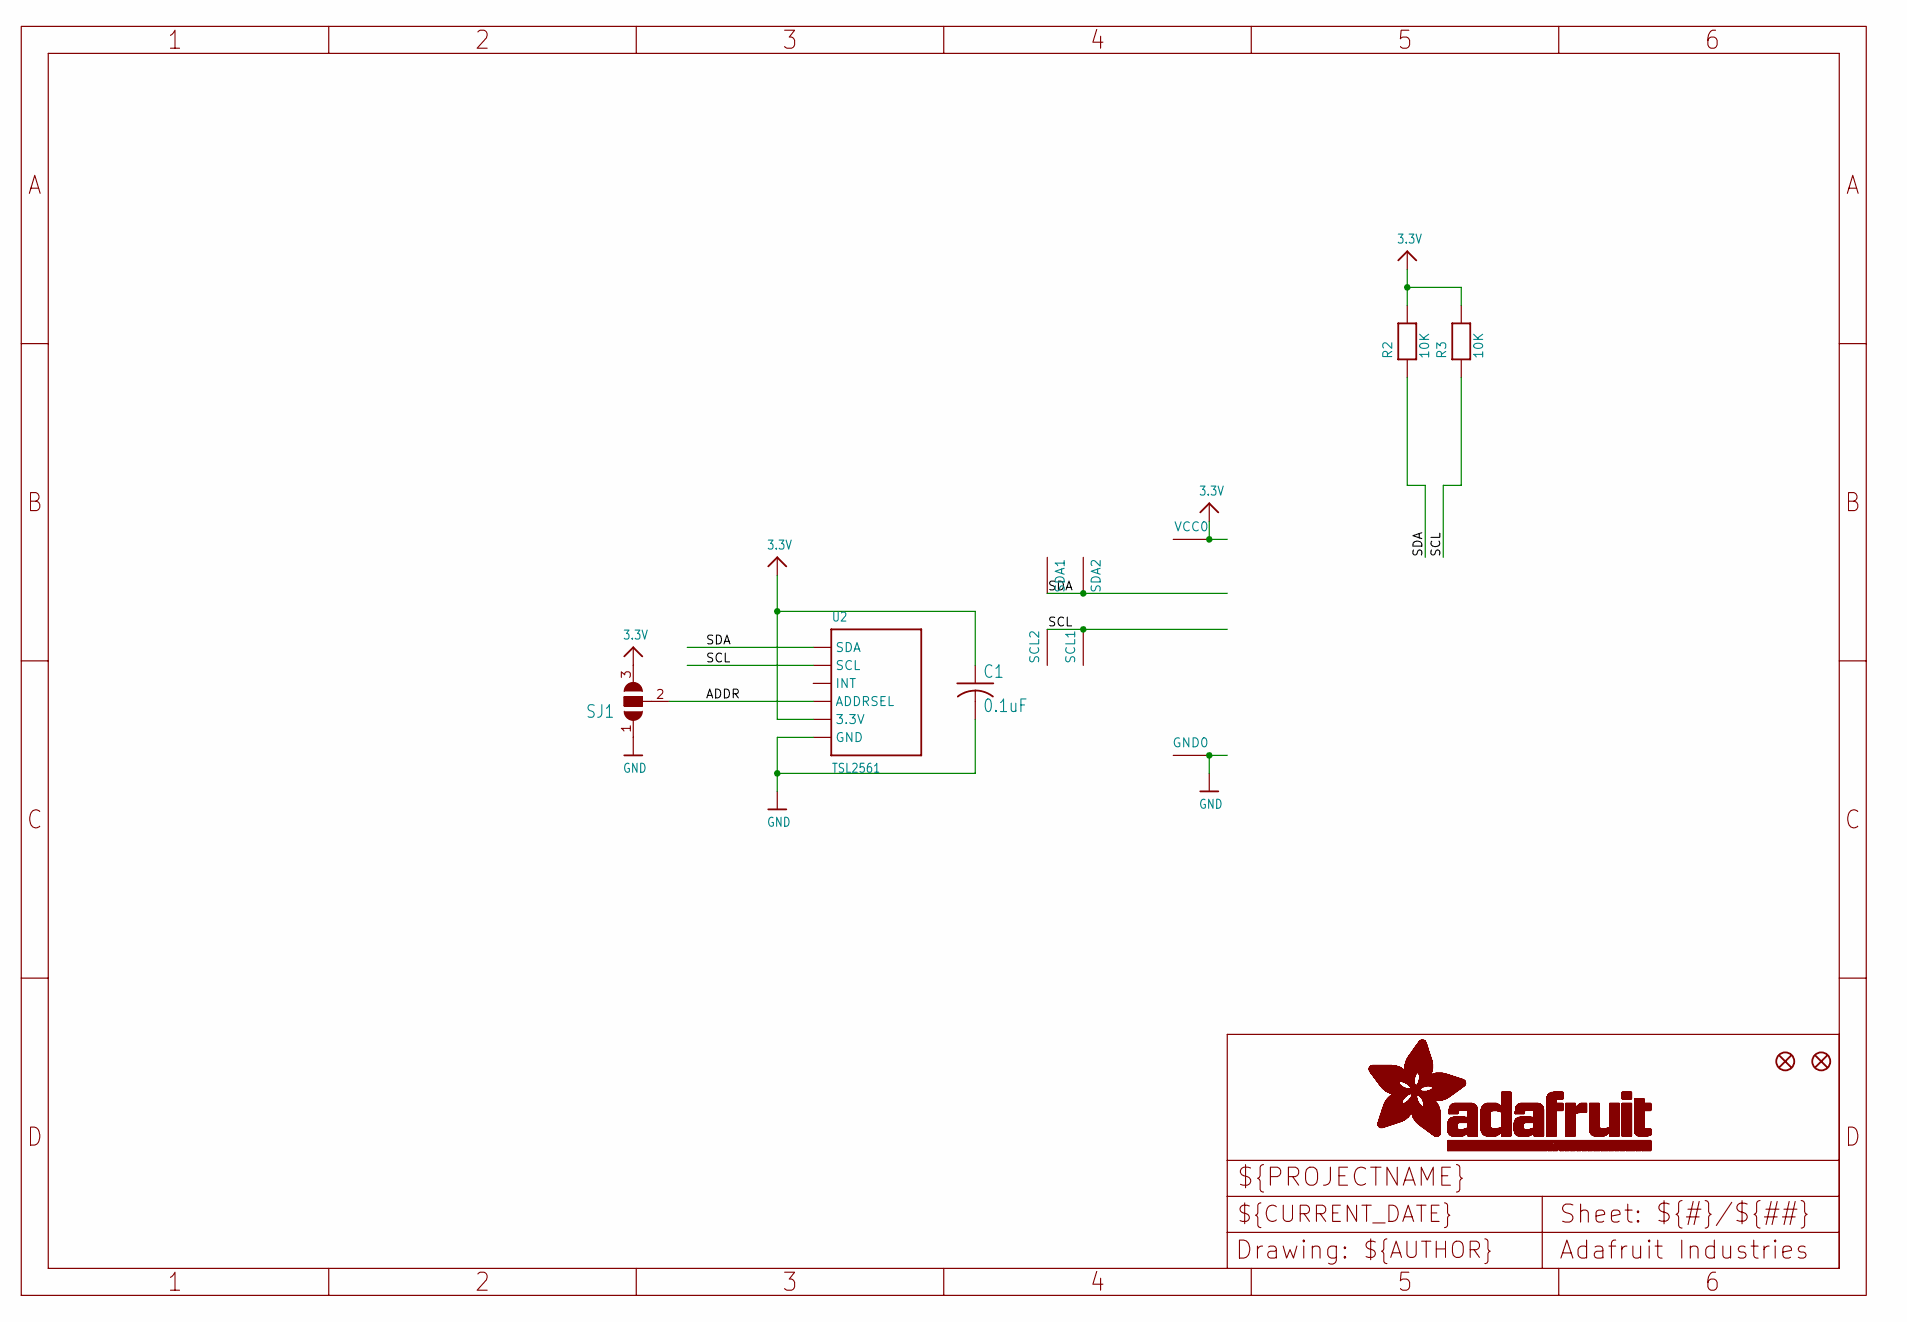
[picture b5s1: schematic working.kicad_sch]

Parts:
C1: 0.1uF; C0805K
FID1, FID2: FIDUCIAL""; FIDUCIAL_1MM
GND0: SEWTAP0.5IN; SEWINGTAP_0.5
R2, R3: 10K; _0805
SCL1, SCL2: SEWTAP0.5IN; SEWINGTAP_0.5
SDA1, SDA2: SEWTAP0.5IN; SEWINGTAP_0.5
SJ1: SJ2W; SJ_2
U2: TSL2561; TSL2561_FN
VCC0: SEWTAP0.5IN; SEWINGTAP_0.5

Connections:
3.3V: C1.1, R2.2, R3.2, SJ1.3, U2.VDD (3.3V), VCC0.TAP
ADDR: SJ1.2, U2.ADR (ADDRSEL)
GND: C1.2, GND0.TAP, SJ1.1, U2.VSS (GND)
SCL: R3.1, SCL1.TAP, SCL2.TAP, U2.CLK (SCL)
SDA: R2.1, SDA1.TAP, SDA2.TAP, U2.DATA (SDA)

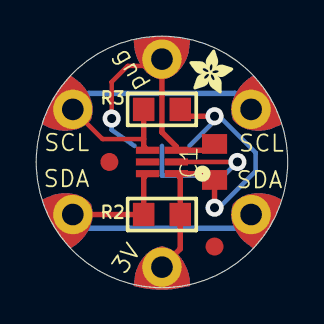
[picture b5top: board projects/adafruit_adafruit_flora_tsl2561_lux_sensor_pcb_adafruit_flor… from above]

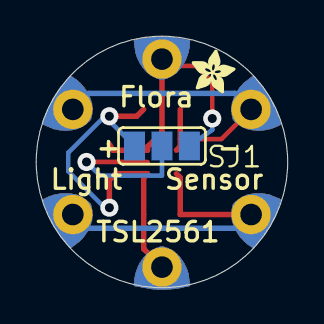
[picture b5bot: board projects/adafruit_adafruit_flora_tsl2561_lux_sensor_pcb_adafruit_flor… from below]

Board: 2 copper layers, 14.0 x 14.0 mm, 15 parts (2 on the bottom side), 5 nets.

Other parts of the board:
U$3, U$4: ADAFRUIT_2.5MM

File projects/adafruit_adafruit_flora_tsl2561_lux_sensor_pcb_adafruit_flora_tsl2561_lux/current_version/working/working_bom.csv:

"Id";"Designator";"Footprint";"Quantity";"Designation";"Supplier and ref";
1;"SDA1,SCL1,SCL2,SDA2,VCC0,GND0";"SEWINGTAP_0.5";6;"SEWTAP0.5IN";;;
2;"R3,R2";"_0805";2;"10K";;;
3;"U$4,U$3";"ADAFRUIT_2.5MM";2;"";;;
4;"U2";"TSL2561_FN";1;"TSL2561";;;
5;"FID2,FID1";"FIDUCIAL_1MM";2;"FIDUCIAL""";;;
6;"C1";"C0805K";1;"0.1uF";;;
7;"SJ1";"SJ_2";1;"";;;
